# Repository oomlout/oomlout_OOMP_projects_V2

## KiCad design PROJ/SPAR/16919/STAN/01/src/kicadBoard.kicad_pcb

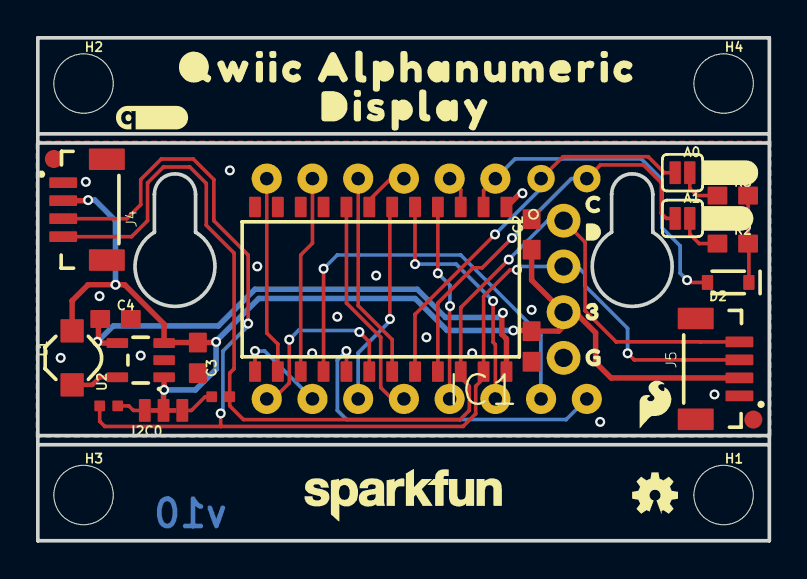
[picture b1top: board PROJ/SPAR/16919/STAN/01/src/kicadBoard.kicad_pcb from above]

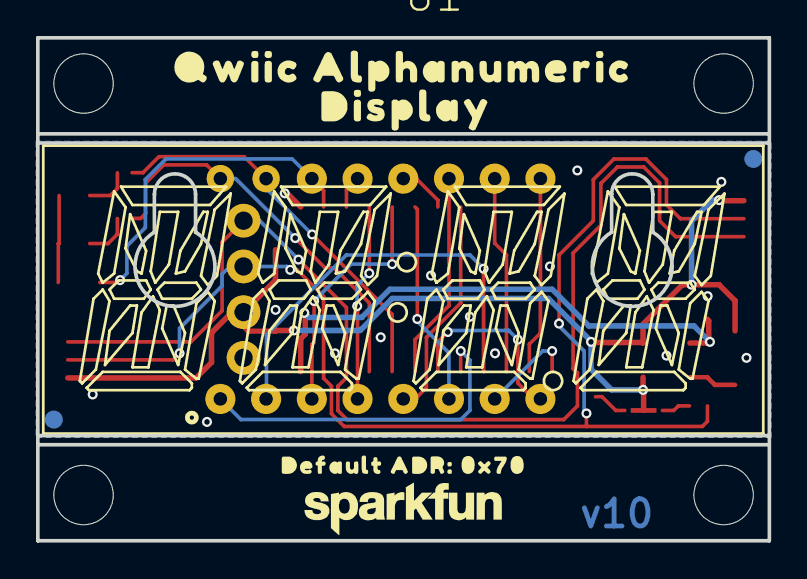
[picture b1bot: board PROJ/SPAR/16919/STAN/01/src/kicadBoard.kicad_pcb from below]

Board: 2 copper layers, 40.6 x 27.9 mm, 46 parts (7 on the bottom side), 27 nets.

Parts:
A0, A1: JUMPER-SMT_2_NO_SILK; SMT-JUMPER_2_NO_SILK
C1: 0.1uF; 0603
C2, C4: 10uF; 0603
C3: 4.7uF; 0603
D2: 250mA/100V; SOD-323
FD1, FD2, FD3, FD4: FIDUCIAL1X2; FIDUCIAL-1X2
FRAME1: FRAME-LETTER; CREATIVE_COMMONS
H1, H2, H3, H4: STAND-OFF
I2C0: JUMPER-SMT_3_2-NC_TRACE_NO-SILK; SMT-JUMPER_3_2-NC_TRACE_NO-SILK
IC1: VK16K33
J3: 1X04_NO_SILK
J4, J5: Vertical Qwiic Connector; JST04_1MM_VERT
L1: 4.7µH; INDUCTOR_4.7UH
LOGO1: OSHW-LOGOMINI; OSHW-LOGO-MINI
LOGO2, LOGO3: SFE_LOGO_NAME.1_INCH; SFE_LOGO_NAME_.1
LOGO4: SFE_LOGO_FLAME.1_INCH; SFE_LOGO_FLAME_.1
R2, R3: 39k; 0603
R4, R5: 4.7k; 0402-TIGHT
U1: Alphanumeric Display; SILSMART_DISPLAY
U2: XC9140; SOT23-5
U$1: DEFAULT_ADR#_0X700
U$3, U$7: MOUNTING_HOLE_M2-0.4X6
U$6: QWIIC_4MM
U$8, U$9: QWIIC_ALPHANUMERIC0
U$10, U$11: DISPLAY0
U$12: #A0#0
U$13: #A1#0
U$14: C0
U$15: D0
U$16: 30
U$17: G0

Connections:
3.3V: C1.1, C2.1, C3.1, I2C0.2, J3.2, J4.2, J5.2, L1.P$2, U2.1, U2.3
5V: C4.1, IC1.24, U2.4
COM_A: D2.A, IC1.2, U1.14
COM_B: IC1.3, U1.13
COM_C: IC1.4, U1.4
COM_D: IC1.5, U1.3
COM_E: IC1.6, U1.6
COM_F: IC1.7, U1.12
COM_G: IC1.8, U1.5
DIG_1A: A1.1, IC1.21, U1.16
DIG_1B: IC1.17, U1.1
DIG_2A: A0.1, IC1.20, U1.15
DIG_2B: IC1.16, U1.2
DIG_3A: IC1.19, U1.11
DIG_3B: IC1.15, U1.10
DIG_4A: IC1.18, U1.8
DIG_4B: IC1.14, U1.9
DIG_DP: IC1.13, U1.7
GND: C1.2, C2.2, C3.2, C4.2, IC1.1, J3.1, J4.1, J5.1, U2.2
unnamed: I2C0.3, R4.2
unnamed: A1.2, R2.1
unnamed: A0.2, R3.1
unnamed: I2C0.1, R5.2
unnamed: D2.C, R2.2, R3.2
unnamed: L1.P$1, U2.5
SCL: IC1.22, J3.4, J4.4, J5.4, R5.1
SDA: IC1.23, J3.3, J4.3, J5.3, R4.1

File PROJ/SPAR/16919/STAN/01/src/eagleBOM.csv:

"Part";"Value";"Device";"Package";"Description";"DESIGNER";"PROD_ID";"REV";"VALUE";
"A0";"JUMPER-SMT_2_NO_SILK";"JUMPER-SMT_2_NO_SILK";"SMT-JUMPER_2_NO_SILK";"Normally open jumper";"";"";"";"";
"A1";"JUMPER-SMT_2_NO_SILK";"JUMPER-SMT_2_NO_SILK";"SMT-JUMPER_2_NO_SILK";"Normally open jumper";"";"";"";"";
"C1";"0.1uF";"0.1UF-0603-25V-5%";"0603";"0.1µF ceramic capacitors";"";"CAP-08604";"";"0.1uF";
"C2";"10uF";"10UF-0603-6.3V-20%";"0603";"10.0µF ceramic capacitors";"";"CAP-11015";"";"10uF";
"C3";"4.7uF";"4.7UF-0603-6.3V-(10%)";"0603";"4.7µF ceramic capacitors";"";"CAP-08280";"";"4.7uF";
"C4";"10uF";"10UF-0603-6.3V-20%";"0603";"10.0µF ceramic capacitors";"";"CAP-11015";"";"10uF";
"D2";"250mA/100V";"DIODE-BAS16J";"SOD-323";"Diode";"";"DIO-09646";"";"250mA/100V";
"FD1";"FIDUCIAL1X2";"FIDUCIAL1X2";"FIDUCIAL-1X2";"Fiducial Alignment Points";"";"";"";"";
"FD2";"FIDUCIAL1X2";"FIDUCIAL1X2";"FIDUCIAL-1X2";"Fiducial Alignment Points";"";"";"";"";
"FD3";"FIDUCIAL1X2";"FIDUCIAL1X2";"FIDUCIAL-1X2";"Fiducial Alignment Points";"";"";"";"";
"FD4";"FIDUCIAL1X2";"FIDUCIAL1X2";"FIDUCIAL-1X2";"Fiducial Alignment Points";"";"";"";"";
"FRAME1";"FRAME-LETTER";"FRAME-LETTER";"CREATIVE_COMMONS";"Schematic Frame - Letter";"";"";"";"";
"H1";"STAND-OFF";"STAND-OFF";"STAND-OFF";"Stand Off";"";"";"";"";
"H2";"STAND-OFF";"STAND-OFF";"STAND-OFF";"Stand Off";"";"";"";"";
"H3";"STAND-OFF";"STAND-OFF";"STAND-OFF";"Stand Off";"";"";"";"";
"H4";"STAND-OFF";"STAND-OFF";"STAND-OFF";"Stand Off";"";"";"";"";
"I2C";"JUMPER-SMT_3_2-NC_TRACE_NO-SILK";"JUMPER-SMT_3_2-NC_TRACE_NO-SILK";"SMT-JUMPER_3_2-NC_TRACE_NO-SILK";"Normally closed trace jumper (2 of 2 connections)";"";"";"";"";
"IC1";"";"VK16K33VK16K33";"VK16K33";"HT16K33 24 SOP-A : RAM Mapping 16x8";"";"IC-16176";"";"";
"J3";"";"I2C_STANDARD_NO_SILK";"1X04_NO_SILK";"SparkFun I2C Standard Pinout Header";"";"";"";"";
"J4";"Vertical Qwiic Connector";"QWIIC_CONNECTOR";"JST04_1MM_VERT";"SparkFun I2C Standard Qwiic Connector";"";"CONN-14483";"";"Vertical Qwiic Connector";
"J5";"Vertical Qwiic Connector";"QWIIC_CONNECTOR";"JST04_1MM_VERT";"SparkFun I2C Standard Qwiic Connector";"";"CONN-14483";"";"Vertical Qwiic Connector";
"L1";"4.7µH";"INDUCTOR-CDRH-4.7UH";"INDUCTOR_4.7UH";"Inductors";"";"NDUC-10146";"";"4.7µH/±30%/1.2A";
"LOGO1";"OSHW-LOGOMINI";"OSHW-LOGOMINI";"OSHW-LOGO-MINI";"Open-Source Hardware (OSHW) Logo";"";"";"";"";
"LOGO2";"SFE_LOGO_NAME.1_INCH";"SFE_LOGO_NAME.1_INCH";"SFE_LOGO_NAME_.1";"SparkFun Font Logo";"";"";"";"";
"LOGO3";"SFE_LOGO_NAME.1_INCH";"SFE_LOGO_NAME.1_INCH";"SFE_LOGO_NAME_.1";"SparkFun Font Logo";"";"";"";"";
"LOGO4";"SFE_LOGO_FLAME.1_INCH";"SFE_LOGO_FLAME.1_INCH";"SFE_LOGO_FLAME_.1";"SparkFun Flame Logo";"";"";"";"";
"R2";"39k";"39KOHM-0603-1/10W-1%";"0603";"39kΩ resistor";"";"RES-12377";"";"39k";
"R3";"39k";"39KOHM-0603-1/10W-1%";"0603";"39kΩ resistor";"";"RES-12377";"";"39k";
"R4";"4.7k";"4.7KOHM-0402T-1/16W-1%";"0402-TIGHT";"4.7kΩ resistor";"";"RES-15343";"";"4.7k";
"R5";"4.7k";"4.7KOHM-0402T-1/16W-1%";"0402-TIGHT";"4.7kΩ resistor";"";"RES-15343";"";"4.7k";
"U$3";"MOUNTING_HOLE_M2-0.4X6";"MOUNTING_HOLE_M2-0.4X6";"MOUNTING_HOLE_M2-0.4X6";"";"";"";"";"";
"U$7";"MOUNTING_HOLE_M2-0.4X6";"MOUNTING_HOLE_M2-0.4X6";"MOUNTING_HOLE_M2-0.4X6";"";"";"";"";"";
"U1";"Alphanumeric Display";"SILSMART_DISPLAY-PINK";"SILSMART_DISPLAY";"14-Segment Alphanumeric LED Display from Silsmart Optoelectronics";"";"COMP-14892";"";"Alphanumeric Display";
"U2";"XC9140";"XC9140";"SOT23-5";"Simple 100mA max DC boost requiring only 3 external components. Useful for converting 3.3V or 4.2V up to 5V. 5.5V max output.";"";"VREG-14648";"";"";

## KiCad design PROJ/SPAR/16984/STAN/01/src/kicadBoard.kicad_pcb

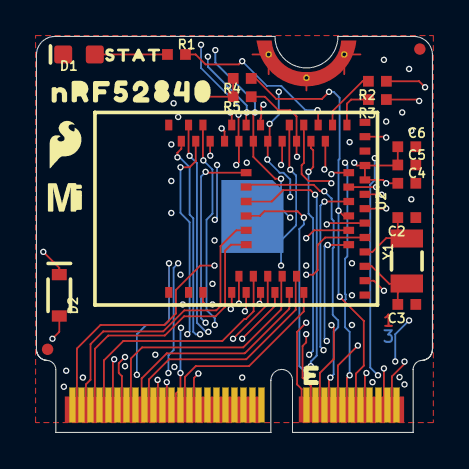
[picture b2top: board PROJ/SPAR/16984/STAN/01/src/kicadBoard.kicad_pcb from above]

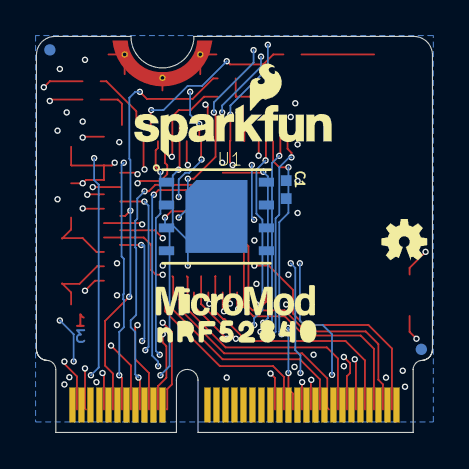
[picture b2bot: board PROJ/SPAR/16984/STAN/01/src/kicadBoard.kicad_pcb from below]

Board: 4 copper layers, 22.0 x 22.0 mm, 31 parts (8 on the bottom side), 59 nets.

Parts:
C1, C6: 0.1uF; 0402-TIGHT
C2, C3: 15pF; 0402-TIGHT
C4, C5: 10uF; 0402-TIGHT
D1: BLUE; LED-0603
D2: 1A/23V/620mV; SOD-323
FD1, FD2, FD3, FD4: FIDUCIALUFIDUCIAL; FIDUCIAL-MICRO
FRAME1: FRAME-LEDGER; CREATIVE_COMMONS
J1: MICROMOD-2222; M.2-CARD-E-22
LOGO1: SFE_LOGO_NAME_FLAME.1_INCH; SFE_LOGO_NAME_FLAME_.1
LOGO2: SFE_LOGO_FLAME.1_INCH; SFE_LOGO_FLAME_.1
LOGO3: OSHW-LOGOMINI; OSHW-LOGO-MINI
LOGO4: SPECIAL_INSTRUCTIONS-ORDERING; ORDERING_INSTRUCTIONS
R1: 1k; 0402-TIGHT
R2, R3: 27OHM; 0402-TIGHT
R4, R5: 10k; 0402-TIGHT
U1: W25QXX128MBIT-6X5; WSON-8-6X5
U2: MDBT50Q
U$1: MICROMOD_MI_LOGO_.35
U$2: STAT0
U$3, U$6: NRF528400
U$5: MICROMOD_LOGO_.35
Y1: 32.768kHz; CRYSTAL-SMD-3.2X1.5MM

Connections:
3.3V: C1.1, C4.1, C5.1, C6.1, D2.C, J1.72, R4.2, R5.2, U1.8, U2.28, U2.30
3.3V_EN: J1.4, U2.8
ADC0: J1.34, U2.20
ADC1: J1.38, U2.21
BATT_VIN/3: J1.49, U2.14
CTS1: J1.15, U2.26
D0: J1.10, U2.16
D1: J1.18, U2.25
FLASH_~CS: U1.1, U2.29
GND: C1.2, C2.1, C3.1, C4.2, C5.2, C6.2, D1.C, J1.1, J1.7, J1.33, J1.36, J1.39, J1.45, J1.75, J1.GND1, J1.GND2, J1.GND3, U1.4, U2.1, U2.2, U2.15, U2.33, U2.55
GPIO0: J1.40, U2.10
GPIO1: J1.42, U2.9
GPIO2: J1.44, U2.6
GPIO3: J1.46, U2.5
GPIO4: J1.48, U2.4
GPIO5: J1.73, U2.41
GPIO6: J1.71, U2.57
GPIO7: J1.69, U2.56
GPIO8: J1.67, U2.7
GPIO9/NFC1: J1.65, U2.52
GPIO10/NFC2: J1.63, U2.54
I2C_~INT: J1.16, U2.39
LED_BUILTIN: R1.2, U2.37
unnamed: R2.2, U2.35
unnamed: D1.A, R1.1
unnamed: R3.2, U2.34
unnamed: C3.2, U2.17, Y1.P$1
unnamed: D2.A, J1.2, J1.74
unnamed: C2.2, U2.18, Y1.P$2
PDM_CLK: J1.50, U2.49
PDM_DATA: J1.52, U2.19
PWM0: J1.32, U2.22
PWM1: J1.47, U2.38
RTS1: J1.13, U2.50
RX1: J1.19, U2.3
RX2: J1.20, U2.59
SCL: J1.14, U2.27
SCL1: J1.53, U2.48
SDA: J1.12, U2.24
SDA1: J1.51, U2.61
SDIO_DATA1: J1.66, U2.46
SDIO_DATA2: J1.68, U1.3, U2.45
SPI_CIPO: J1.61, U2.11
SPI_CIPO1/SDIO_DATA0: J1.64, U1.2, U2.43
SPI_COPI: J1.59, U2.12
SPI_COPI1/SDIO_CMD: J1.62, U1.5, U2.36
SPI_SCK: J1.57, U2.13
SPI_SCK1/SDIO_CLK: J1.60, U1.6, U2.42
SPI_~CS1/SDIO_DATA3: J1.70, U1.7, U2.47
SPI_~CS: J1.55, U2.44
SWDCK: J1.21, U2.53
SWDIO: J1.23, U2.51
TX1: J1.17, U2.60
TX2: J1.22, U2.58
USB_D+: J1.3, R2.1
USB_D-: J1.5, R3.1
V_USB: J1.9, U2.32
~BOOT: J1.11, R4.1, U2.23
~RESET: J1.6, R5.1, U2.40

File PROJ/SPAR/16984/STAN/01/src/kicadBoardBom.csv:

"Id";"Designator";"Package";"Quantity";"Designation";"Supplier and ref";
1;"R1";"0402-TIGHT";1;"1k";;;
2;"R5,R4";"0402-TIGHT";2;"10k";;;
3;"J1";"M.2-CARD-E-22";1;"MICROMOD-2222";;;
4;"R3,R2";"0402-TIGHT";2;"27OHM";;;
5;"U$6,U$3";"NRF528400";2;"";;;
6;"Y1";"CRYSTAL-SMD-3.2X1.5MM";1;"32.768kHz";;;
7;"D2";"SOD-323";1;"1A/23V/620mV";;;
8;"C2,C3";"0402-TIGHT";2;"15pF";;;
9;"C4,C5";"0402-TIGHT";2;"10uF";;;
10;"U$1";"MICROMOD_MI_LOGO_.35";1;"";;;
11;"FD1,FD2,FD3,FD4";"FIDUCIAL-MICRO";4;"FIDUCIALUFIDUCIAL";;;
12;"FRAME1";"CREATIVE_COMMONS";1;"FRAME-LEDGER";;;
13;"C6,C1";"0402-TIGHT";2;"0.1uF";;;
14;"LOGO2";"SFE_LOGO_FLAME_.1";1;"SFE_LOGO_FLAME.1_INCH";;;
15;"D1";"LED-0603";1;"BLUE";;;
16;"U2";"MDBT50Q";1;"MDBT50Q";;;
17;"LOGO4";"ORDERING_INSTRUCTIONS";1;"SPECIAL_INSTRUCTIONS-ORDERING";;;
18;"U$2";"STAT0";1;"";;;
19;"U1";"WSON-8-6X5";1;"W25QXX128MBIT-6X5";;;
20;"LOGO3";"OSHW-LOGO-MINI";1;"OSHW-LOGOMINI";;;
21;"LOGO1";"SFE_LOGO_NAME_FLAME_.1";1;"SFE_LOGO_NAME_FLAME.1_INCH";;;
22;"U$5";"MICROMOD_LOGO_.35";1;"";;;

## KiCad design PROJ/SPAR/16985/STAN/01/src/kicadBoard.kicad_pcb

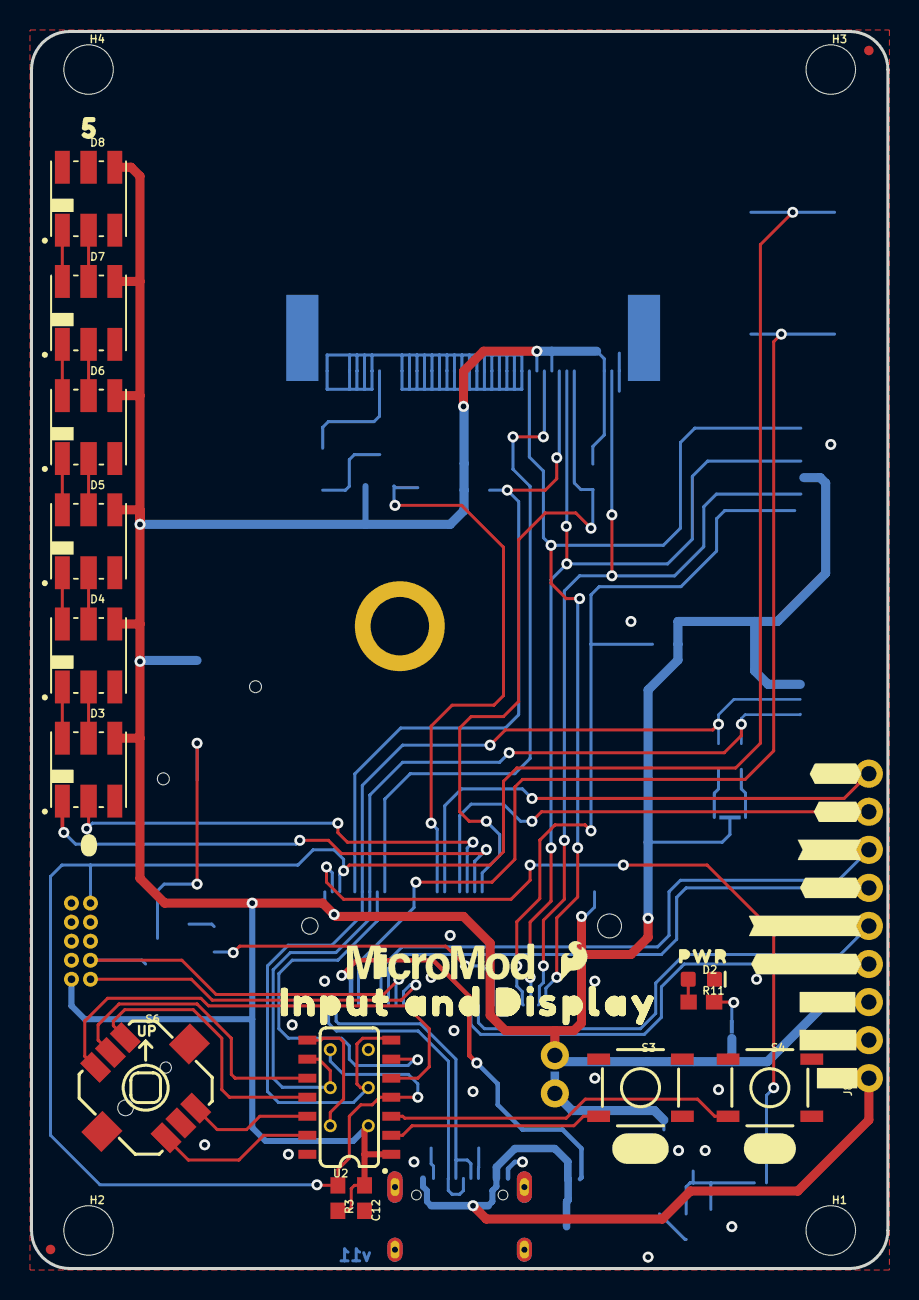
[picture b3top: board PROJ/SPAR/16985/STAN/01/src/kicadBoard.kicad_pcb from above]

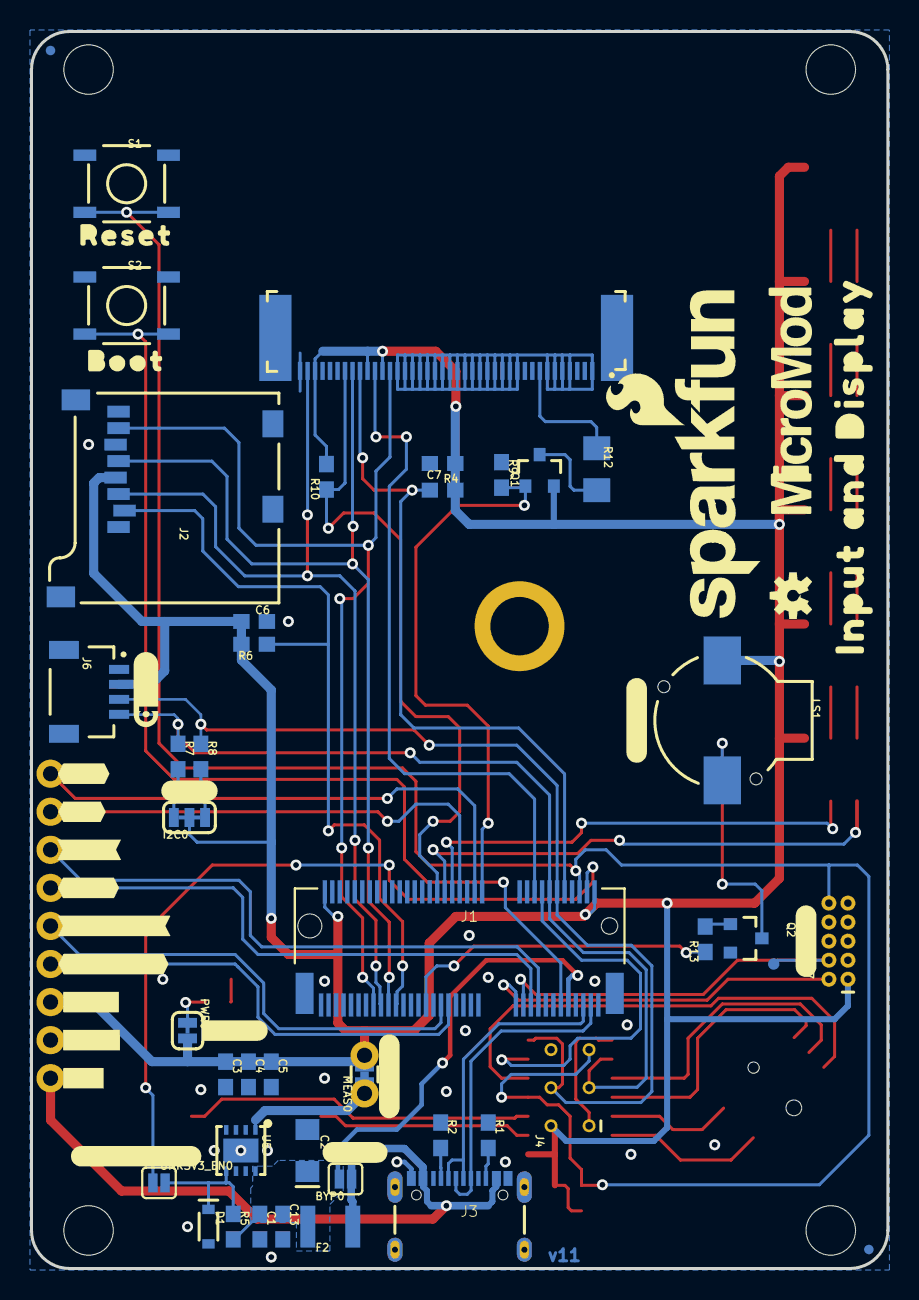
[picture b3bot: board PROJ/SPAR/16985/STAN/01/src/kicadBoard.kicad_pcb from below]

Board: 2 copper layers, 57.1 x 82.6 mm, 107 parts (66 on the bottom side), 61 nets.

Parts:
BYP0: JUMPER-SMT_2_NO_SILK; SMT-JUMPER_2_NO_SILK
C1, C4, C6, C7, C12: 0.1uF; 0603
C2: 10uF; EIA3216
C3: 1.0uF; 0603
C5, C13: 0.22uF; 0603
D1: 3.3V; SOD-323
D2: RED; LED-0603
D3, D4, D5, D6, D7, D8: APA102-5050
F2: 6V/2A; 1210
FD1, FD2, FD3, FD4: FIDUCIALUFIDUCIAL; FIDUCIAL-MICRO
FRAME1: FRAME-LETTER; CREATIVE_COMMONS
FRAME2: FRAME-LETTERNO_PACKAGE; DUMMY
H1, H2, H3, H4: STAND-OFF
H5: STAND-OFF; STAND-OFF-REFLOW-M2.5
I2C0: SMT-JUMPER_3_2-NC_TRACE_SILK
J1: MICROMOD-2222-C; M.2-CONNECTOR-E
J2: MICRO-SD; MICRO-SD-SOCKET
J3: USB-C_Prog; USB-C-16P-2LAYER-PADS
J4: AVR_SPI_PROG_3X2TESTPOINTS; 2X3_TEST_POINTS
J5: 2.4" TFT; FPC05040-17204
J6: QWIIC_RA; JST04_1MM_RA
J7: CORTEX_JTAG_DEBUG; 2X5-PTH-1.27MM-NO_SILK
J8: 1X09_NO_SILK
LOGO1: SFE_LOGO_NAME_FLAME.2_INCH; SFE_LOGO_NAME_FLAME_.2
LOGO2: QWIIC_LOGO_5MM; QWIIC_5MM
LOGO3: OSHW-LOGOS; OSHW-LOGO-S
LS1: Buzzer; BUZZER-CCV
MEAS0: COMBO-JUMPER_2_NC_TRACE
PWR0: SMT-JUMPER_2_NC_TRACE_SILK
Q1: 1.1A/600mΩ; SOT23-3
Q2: 600mA/40V; SOT23-3
R1, R2: 5.1k; 0603
R3, R4, R5, R6, R9, R10: 100k; 0603
R7, R8: 2.2k; 0603
R11, R13: 1k; 0603
R12: 10; 1206
S1: Reset; TACTILE_SWITCH_SMD_5.2MM
S2: BOOT; TACTILE_SWITCH_SMD_5.2MM
S3, S4: MOMENTARY-SWITCH-SPST-SMD-5.2MM-TALL; TACTILE_SWITCH_SMD_5.2MM
S6: Joystick; JOYSTICK_MINI
TP1: PAD.03X.03
U2: ATTINY84; SO14
U5: AP7361C-33FGE; UDFN-8
U$1: MICROMOD_LOGO_.5
U$2, U$16, U$17: INPUT_AND_DISPLAY0
U$3: SFE_LOGO_FLAME_.1
U$4: BOOT0
U$5: #A#0
U$6: #B#0
U$7: 00
U$8: 50
U$9: RESET0
U$10: MICROMOD_LOGO_.6
U$11: #MEAS#0
U$12: #I2C#0
U$13: PWR0
U$14: #BYP#0
U$15: #SWD#0
U$18, U$38: #5V#0
U$19: #PWR#0
U$20: #3V3_CTRL#0
U$21: #PWM1#0
U$22, U$23: #A0#0
U$24, U$25: #A1#0
U$26, U$27: #TX1#0
U$28, U$31: #3V3#0
U$29, U$30: #GND#0
U$32, U$33: #RX1#0
U$34, U$35: #CAN#RX#0
U$36, U$37: #CAN#TX#0
UNK3V3_EN0: SMT-JUMPER_2_NO_SILK

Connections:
3.3V: C3.1, C4.1, C5.1, C6.1, C7.1, C12.1, D3.P4, D4.P4, D5.P4, D6.P4, D7.P4, D8.P4, I2C0.2, J1.2, J1.74, J2.VCC, J4.2, J5.29, J5.31, J5.38, J6.2, J7.1, J8.3, LS1.+, MEAS0.2, MEAS0.4, PWR0.2, Q1.2, R3.2, R4.2, R6.2, R10.2, U2.1
3.3V_EN: J1.4, UNK3V3_EN0.1
A0: J1.34, J8.9
A1: J1.38, J8.8
BTN_A: S3.3, U2.2
BTN_B: S4.3, U2.3
BTN_CENTER: S6.CTR, U2.10
BTN_DOWN: S6.D, U2.13
BTN_LEFT: S6.C, U2.5
BTN_RIGHT: S6.B, U2.12
BTN_UP: S6.A, U2.11
BUZZER: J1.47, R13.1
CAN-RX: J1.41, J8.4
CAN-TX: J1.43, J8.5
DISP_D/~C: J1.18, J5.30
ENABLE: D1.C, R5.1, U5.5, UNK3V3_EN0.2
GND: C1.2, C2.-, C3.2, C4.2, C5.2, C6.2, C7.2, C12.2, C13.2, D1.A, D2.C, D3.P3, D4.P3, D5.P3, D6.P3, D7.P3, D8.P3, H5.1, J1.1, J1.7, J1.33, J1.36, J1.39, J1.45, J1.75, J2.CD1, J2.GND, J3.GND, J3.GND2, J4.6, J5.1, J5.4, J5.5, J5.6, J5.7, J5.11, J5.12, J5.13, J5.14, J5.15, J5.16, J5.17, J5.18, J5.19, J5.20, J5.21, J5.22, J5.23, J5.24, J5.25, J5.26, J5.27, J5.40, J6.1, J7.3, J7.5, J7.9, J8.2, Q2.2, R1.1, R2.1, R9.1, S1.1, S1.2, S2.1, S2.2, S3.1, S4.1, S6.GND, U2.14, U5.4, U5.EP
LED_CLK: D3.P2, J1.40
LED_DATA: D3.P1, J1.42
MISO_ATTINY: J4.1, U2.8
unnamed: I2C0.3, R7.2
unnamed: I2C0.1, R8.2
unnamed: J5.8, R12.1
unnamed: Q1.3, R12.2
unnamed: LS1.-, Q2.3
unnamed: Q2.1, R13.2
unnamed: D3.P5, D4.P2
unnamed: D3.P6, D4.P1
unnamed: J3.A5, R2.2
unnamed: J3.B5, R1.2
unnamed: PWR0.1, R11.2
unnamed: D2.A, R11.1
unnamed: MEAS0.1, MEAS0.3, U5.1
unnamed: D4.P5, D5.P2
unnamed: D4.P6, D5.P1
unnamed: D5.P5, D6.P2
unnamed: D5.P6, D6.P1
unnamed: D6.P5, D7.P2
unnamed: D6.P6, D7.P1
unnamed: D7.P5, D8.P2
unnamed: D7.P6, D8.P1
RX1: J1.19, J8.6
SCL: J1.14, J4.3, J6.4, R7.1, U2.9
SDA: J1.12, J4.4, J6.3, R8.1, U2.7
SPI_CIPO: J1.61, J2.DO, J5.28
SPI_COPI: J1.59, J2.DI, J5.39
SPI_SCK: J1.57, J2.SCLK, J5.33
SWDCK: J1.21, J7.4, TP1.P$1
SWDIO: J1.23, J7.2
TX1: J1.17, J8.7
USB_D+: J1.3, J3.A6, J3.B6
USB_D-: J1.5, J3.A7, J3.B7
VIN: BYP0.2, C1.1, C2.+, C13.1, F2.2, J1.9, R5.2, U5.8
V_USB: BYP0.1, F2.1, J3.VBUS1, J3.VBUS2, J8.1
~BOOT: J1.11, S2.3, S2.4
~DISP_BL: J1.32, Q1.1, R9.2
~DISP_CS: J1.10, J5.32, R4.1
~DISP_RST: J1.44, J5.34, R10.1
~INT: J1.16, U2.6
~RESET: J1.6, J4.5, J7.10, R3.1, S1.3, S1.4, U2.4
~SD_CS: J1.55, J2.CS, R6.1

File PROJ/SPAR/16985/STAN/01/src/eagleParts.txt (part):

Partlist

Exported from boardEagle.brd at 20/08/2022 16:38

EAGLE Version 9.6.2 Copyright (c) 1988-2020 Autodesk, Inc.

Assembly variant: 

Part     Value                                Package                      Library                     Position (inch)       Orientation

3V3_EN                                        SMT-JUMPER_2_NO_SILK         SparkFun-Jumpers            (1.915 0.225)         MR0
BYP      JUMPER-SMT_2_NO_SILK                 SMT-JUMPER_2_NO_SILK         SparkFun-Jumpers            (1.425 0.235)         MR180
C1       0.1uF                                0603                         SparkFun-Capacitors         (1.65 0.11)           MR270
C2       10uF                                 EIA3216                      SparkFun-Capacitors         (1.525 0.31)          MR270
C3       1.0uF                                0603                         SparkFun-Capacitors         (1.74 0.51)           MR270
C4       0.1uF                                0603                         SparkFun-Capacitors         (1.68 0.51)           MR270
C5       0.22uF                               0603                         SparkFun-Capacitors         (1.62 0.51)           MR270
C6       0.1uF                                0603                         SparkFun-Capacitors         (1.665 1.7)           MR0
C7       0.1uF                                0603                         SparkFun-Capacitors         (1.17 2.115)          MR180
C12      0.1uF                                0603                         SparkFun-Capacitors         (0.875 0.185)         R270
C13      0.22uF                               0603                         SparkFun-Capacitors         (1.59 0.11)           MR270
D1       3.3V                                 SOD-323                      SparkFun-DiscreteSemi       (1.785 0.11)          MR270
D2       RED                                  LED-0603                     SparkFun-LED                (1.76 0.76)           R0
D3       APA102-5050                          APA102-5050                  SparkFun-LED                (0.15 1.31062992)     R0
D4       APA102-5050                          APA102-5050                  SparkFun-LED                (0.15 1.61062992)     R0
D5       APA102-5050                          APA102-5050                  SparkFun-LED                (0.15 1.91062992)     R0
D6       APA102-5050                          APA102-5050                  SparkFun-LED                (0.15 2.21062992)     R0
D7       APA102-5050                          APA102-5050                  SparkFun-LED                (0.15 2.51062992)     R0
D8       APA102-5050                          APA102-5050                  SparkFun-LED                (0.15 2.81062992)     R0
F2       6V/2A                                1210                         SparkFun-Fuses              (1.465 0.11)          MR180
FD1      FIDUCIALUFIDUCIAL                    FIDUCIAL-MICRO               SparkFun-Aesthetics         (0.05 0.05)           MR0
FD2      FIDUCIALUFIDUCIAL                    FIDUCIAL-MICRO               SparkFun-Aesthetics         (0.05 0.05)           R0
FD3      FIDUCIALUFIDUCIAL                    FIDUCIAL-MICRO               SparkFun-Aesthetics         (2.2 3.2)             R0
FD4      FIDUCIALUFIDUCIAL                    FIDUCIAL-MICRO               SparkFun-Aesthetics         (2.2 3.2)             MR0
H5       STAND-OFF                            STAND-OFF-REFLOW-M2.5        SparkFun-Hardware           (0.96771654 1.68759843) MR90
I2C                                           SMT-JUMPER_3_2-NC_TRACE_SILK SparkFun-Jumpers            (1.835 1.185)         MR180
J1       MICROMOD-2222-C                      M.2-CONNECTOR-E              SparkFun-MicroMod           (1.125 0.9)           MR0
J2       MICRO-SD                             MICRO-SD-SOCKET              SparkFun-Connectors         (1.6 2.3)             MR90
J3       USB-C_Prog                           USB-C-16P-2LAYER-PADS        SparkFun-Connectors         (1.125 0.25)          MR0
J4       AVR_SPI_PROG_3X2TESTPOINTS           2X3_TEST_POINTS              SparkFun-Connectors         (0.835 0.475)         MR90
J5       2.4" TFT                             FPC05040-17204               SparkFun-Displays           (1.16043307 2.38188976) MR180
J6       QWIIC_RA                             JST04_1MM_RA                 SparkFun-Connectors         (2.02 1.515)          MR270
J7       CORTEX_JTAG_DEBUG                    2X5-PTH-1.27MM-NO_SILK       SparkFun-Connectors         (0.13 0.86)           MR90
J8                                            1X09_NO_SILK                 SparkFun-Connectors         (2.2 0.5)             R90
LS1      Buzzer                               BUZZER-CCV                   SparkFun-Electromechanical  (0.435 1.44)          MR90
MEAS                                          COMBO-JUMPER_2_NC_TRACE      SparkFun-Jumpers            (1.375 0.51)          MR90
PWR                                           SMT-JUMPER_2_NC_TRACE_SILK   SparkFun-Jumpers            (1.84 0.625)          MR270
Q1       1.1A/600m?                           SOT23-3                      SparkFun-DiscreteSemi       (0.915 2.095)         MR0
Q2       600mA/40V                            SOT23-3                      SparkFun-DiscreteSemi       (0.37437008 0.86740157) MR270
R1       5.1k                                 0603                         SparkFun-Resistors          (1.05 0.35)           MR270
R2       5.1k                                 0603                         SparkFun-Resistors          (1.175 0.35)          MR270
R3       100k                                 0603                         SparkFun-Resistors          (0.805 0.185)         R270
R4       100k                                 0603                         SparkFun-Resistors          (1.17 2.045)          MR0
R5       100k                                 0603                         SparkFun-Resistors          (1.72 0.11)           MR270
R6       100k                                 0603                         SparkFun-Resistors          (1.665 1.64)          MR180
R7       2.2k                                 0603                         SparkFun-Resistors          (1.865 1.345)         MR270
R8       2.2k                                 0603                         SparkFun-Resistors          (1.805 1.345)         MR270
R9       100k                                 0603                         SparkFun-Resistors          (1.015 2.085)         MR270
R10      100k                                 0603                         SparkFun-Resistors          (1.475 2.08)          MR90
R11      1k                                   0603                         SparkFun-Resistors          (1.76 0.7)            R0
R12      10                                   1206                         SparkFun-Resistors          (0.765 2.1)           MR270
R13      1k                                   0603                         SparkFun-Resistors          (0.48 0.865)          MR90
S1       Reset                                TACTILE_SWITCH_SMD_5.2MM     SparkFun-Switches           (2 2.85)              MR0
S2       BOOT                                 TACTILE_SWITCH_SMD_5.2MM     SparkFun-Switches           (2 2.53)              MR0
S3       MOMENTARY-SWITCH-SPST-SMD-5.2MM-TALL TACTILE_SWITCH_SMD_5.2MM     SparkFun-Switches           (1.6 0.475)           R0
S4       MOMENTARY-SWITCH-SPST-SMD-5.2MM-TALL TACTILE_SWITCH_SMD_5.2MM     SparkFun-Switches           (1.94 0.475)          R0
S6       Joystick                             JOYSTICK_MINI                SparkFun-Switches           (0.3 0.475)           R315
TP1                                           PAD.03X.03                   SparkFun-Connectors         (0.3 0.8)             MR0
U2       ATTINY84                             SO14                         SparkFun-IC-Microcontroller (0.835 0.45)          R90
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
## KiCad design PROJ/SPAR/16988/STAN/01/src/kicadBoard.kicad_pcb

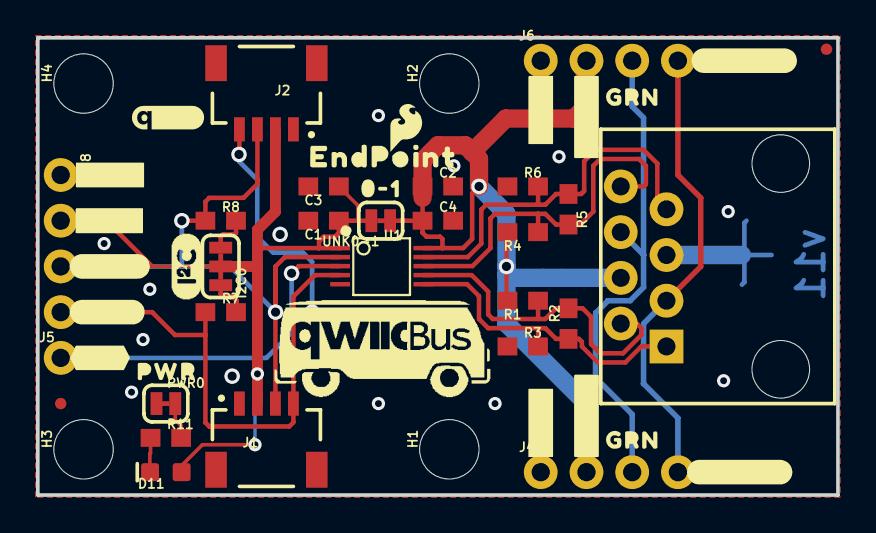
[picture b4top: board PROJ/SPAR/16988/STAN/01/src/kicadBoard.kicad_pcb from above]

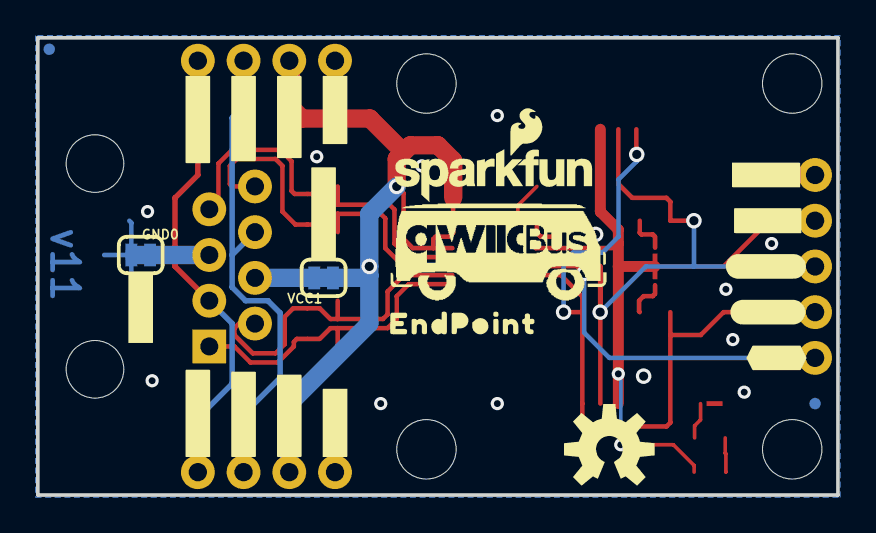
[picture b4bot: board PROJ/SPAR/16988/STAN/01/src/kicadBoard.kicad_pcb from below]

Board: 2 copper layers, 44.5 x 25.4 mm, 76 parts (23 on the bottom side), 18 nets.

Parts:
C1, C2: 0.1uF; 0603
C3, C4: 1.0uF; 0603
D11: RED; LED-0603
FD1, FD2, FD3, FD4: FIDUCIALUFIDUCIAL; FIDUCIAL-MICRO
FRAME1: FRAME-LETTER; CREATIVE_COMMONS
GND0: JUMPER-SMT_2_NC_TRACE_SILK; SMT-JUMPER_2_NC_TRACE_SILK
H1, H2, H3, H4: STAND-OFF
I2C0: JUMPER-SMT_3_2-NC_TRACE_SILK; SMT-JUMPER_3_2-NC_TRACE_SILK
J1, J2: QWIIC; JST04_1MM_RA
J3: RJ45; RJ45-8
J4, J6, J8: 1X04_NO_SILK
J5: 1X01_NO_SILK
LOGO1: OSHW-LOGOM; OSHW-LOGO-M
LOGO2: REVISION
LOGO3: QWIIC_LOGO_4MM; QWIIC_4MM
LOGO4: SFE_LOGO_NAME_FLAME.1_INCH; SFE_LOGO_NAME_FLAME_.1
LOGO5: SFE_LOGO_FLAME.1_INCH; SFE_LOGO_FLAME_.1
PWR0: JUMPER-SMT_2_NC_TRACE_SILK; SMT-JUMPER_2_NC_TRACE_SILK
R1, R3, R4, R6: 390; 0603
R2, R5: 100; 0603
R7, R8: 4.7k; 0603
R11: 1k; 0603
U1: PCA9615; TSSOP10
U$1: I2C
U$2, U$29: GRN0
U$3, U$4, U$5, U$6, U$13, U$33, U$34: #GND#0
U$7, U$8: #3V3#0
U$9, U$15: #SDA#0
U$10, U$16: #SCL#0
U$11, U$17: #EN#0
U$12: #VDDA#0
U$14, U$18: #GND2#0
U$19, U$22: #GRNW#0
U$20, U$21, U$31, U$32: #VCC1#0
U$23, U$28: QWIICBUS#WORKING#LOGO#JPG
U$24, U$30: #VCC2#0
U$25: 0#10
U$26, U$35: ENDPOINT0
U$27: PWR0
UNK0-1: JUMPER-SMT_2_NC_TRACE_SILK; SMT-JUMPER_2_NC_TRACE_SILK
VCC1: JUMPER-SMT_2_NC_TRACE_SILK; SMT-JUMPER_2_NC_TRACE_SILK

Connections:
DSCL_N: J3.1, R2.1, R3.2, U1.6
DSCL_P: J3.2, R1.1, R2.2, U1.7
DSDA_N: J3.7, R5.1, R6.2, U1.9
DSDA_P: J3.8, R4.1, R5.2, U1.8
EN: J5.1, U1.3
GND: C1.2, C2.2, C3.2, C4.2, GND0.1, J1.1, J2.1, J4.1, J6.1, J8.1, PWR0.1, R3.1, R6.1, U1.5
GRN_N: J3.6, J4.3, J6.3
GRN_P: J3.3, J4.4, J6.4
unnamed: J3.4, VCC1.2
unnamed: GND0.2, J3.5
unnamed: I2C0.1, R8.2
unnamed: I2C0.3, R7.2
unnamed: D11.C, R11.1
unnamed: PWR0.2, R11.2
SCL: J1.4, J2.4, J8.4, R7.1, U1.4
SDA: J1.3, J2.3, J8.3, R8.1, U1.2
VCC: C1.1, C3.1, D11.A, I2C0.2, J1.2, J2.2, J8.2, U1.1, UNK0-1.2
VCC_1: C2.1, C4.1, J4.2, J6.2, R1.2, R4.2, U1.10, UNK0-1.1, VCC1.1

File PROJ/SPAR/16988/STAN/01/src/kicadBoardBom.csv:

"Id";"Designator";"Package";"Quantity";"Designation";"Supplier and ref";
1;"R2,R5";"0603";2;"100";;;
2;"R3,R4,R1,R6";"0603";4;"390";;;
3;"UNK0-1,PWR0,GND0,VCC1";"SMT-JUMPER_2_NC_TRACE_SILK";4;"JUMPER-SMT_2_NC_TRACE_SILK";;;
4;"J5";"1X01_NO_SILK";1;"";;;
5;"U$28,U$23";"QWIICBUS#WORKING#LOGO#JPG";2;"";;;
6;"H2,H4,H3,H1";"STAND-OFF";4;"STAND-OFF";;;
7;"U$1";"I2C";1;"";;;
8;"U$2,U$29";"GRN0";2;"";;;
9;"U$22,U$19";"#GRNW#0";2;"";;;
10;"U$34,U$3,U$5,U$4,U$33,U$13,U$6";"#GND#0";7;"";;;
11;"FRAME1";"CREATIVE_COMMONS";1;"FRAME-LETTER";;;
12;"J2,J1";"JST04_1MM_RA";2;"QWIIC";;;
13;"D11";"LED-0603";1;"RED";;;
14;"C3,C4";"0603";2;"1.0uF";;;
15;"U$20,U$32,U$21,U$31";"#VCC1#0";4;"";;;
16;"C1,C2";"0603";2;"0.1uF";;;
17;"FD1,FD2,FD3,FD4";"FIDUCIAL-MICRO";4;"FIDUCIALUFIDUCIAL";;;
18;"J4,J8,J6";"1X04_NO_SILK";3;"";;;
19;"LOGO5";"SFE_LOGO_FLAME_.1";1;"SFE_LOGO_FLAME.1_INCH";;;
20;"I2C0";"SMT-JUMPER_3_2-NC_TRACE_SILK";1;"JUMPER-SMT_3_2-NC_TRACE_SILK";;;
21;"R7,R8";"0603";2;"4.7k";;;
22;"U$10,U$16";"#SCL#0";2;"";;;
23;"LOGO3";"QWIIC_4MM";1;"QWIIC_LOGO_4MM";;;
24;"U$27";"PWR0";1;"";;;
25;"U$11,U$17";"#EN#0";2;"";;;
26;"U$35,U$26";"ENDPOINT0";2;"";;;
27;"U$7,U$8";"#3V3#0";2;"";;;
28;"J3";"RJ45-8";1;"RJ45";;;
29;"R11";"0603";1;"1k";;;
30;"U1";"TSSOP10";1;"PCA9615";;;
31;"LOGO2";"REVISION";1;"REVISION";;;
32;"U$25";"0#10";1;"";;;
33;"U$9,U$15";"#SDA#0";2;"";;;
34;"U$14,U$18";"#GND2#0";2;"";;;
35;"LOGO1";"OSHW-LOGO-M";1;"OSHW-LOGOM";;;
36;"U$30,U$24";"#VCC2#0";2;"";;;
37;"U$12";"#VDDA#0";1;"";;;
38;"LOGO4";"SFE_LOGO_NAME_FLAME_.1";1;"SFE_LOGO_NAME_FLAME.1_INCH";;;

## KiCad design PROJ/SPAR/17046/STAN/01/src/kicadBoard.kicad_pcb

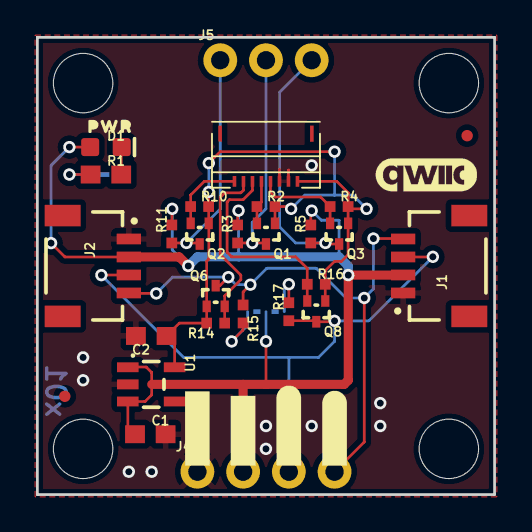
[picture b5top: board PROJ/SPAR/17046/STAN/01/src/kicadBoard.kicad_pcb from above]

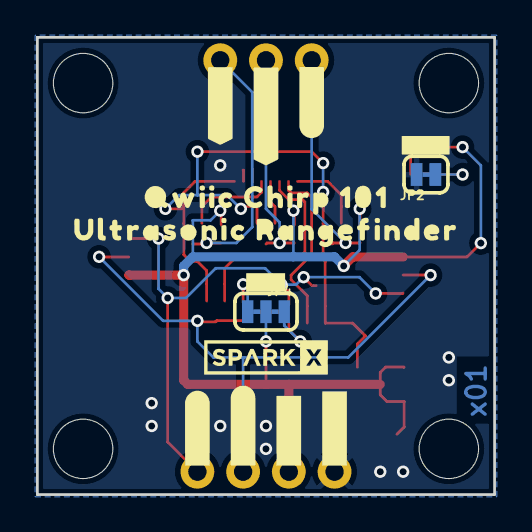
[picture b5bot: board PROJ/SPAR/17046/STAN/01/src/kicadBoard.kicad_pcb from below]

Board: 2 copper layers, 25.4 x 25.4 mm, 49 parts (14 on the bottom side), 17 nets.

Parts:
C1, C2: 1.0uF; 0603
D1: RED; LED-0603
FD1, FD2: FIDUCIALUFIDUCIAL; FIDUCIAL-MICRO
FRAME1: FRAME-LETTERNO_PACKAGE; DUMMY
J1, J2: QWIIC_RIGHT_ANGLE; JST04_1MM_RA
J4: 1X04_NO_SILK
J5: 1X03_NO_SILK
JP2: SMT-JUMPER_2_NC_TRACE_SILK
JP4: I2C PU; SMT-JUMPER_3_2-NC_TRACE_SILK
Q1, Q2, Q3, Q6, Q8: 20V/0.2A/8MHz/1.2Ω/1Vth; SOT-416FL
R1: 1k; 0603
R2, R3, R4, R5, R10, R11, R14, R15, R16, R17: 2.2k; 0402-TIGHT
U1: AP2127K-1.8V; SOT23-5
U$1: MOD-CH101_CONNECTOR; FPC_MOLEX5034800800
U$2: QWIIC_BOARD_OUTLINEH; QWIIC_BOARD_MOUNT_HOLES
U$3, U$13: #_3V3#1
U$4, U$14: #_GND#0
U$5, U$12: #_SDA#2
U$6, U$11: #_SCL#3
U$7: QWIIC_CHIRP_1017
U$8: ULTRASONIC_RANGEFINDER8
U$9: #I�C#1019
U$10: #LED#1018
U$15: ##INT_##0
U$16: ##RST_##1
U$17: #PROG_#5
U$18: SPARKX-SMALL
U$19: QWIIC_COPYRIGHT_SMALL
U$20: PWR0

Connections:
1.8V: C2.1, Q1.1, Q2.1, Q3.1, Q6.1, Q8.1, R2.2, R4.2, R10.2, R14.2, R16.2, U1.5, U$1.1
GND: C1.2, C2.2, J1.1, J2.1, J4.1, JP2.2, U1.2, U$1.2, U$1.3
INT_HI: J5.1, Q2.3, R11.1
INT_LO: Q2.2, R10.1, U$1.8
unnamed: D1.C, R1.2
unnamed: JP4.3, R15.2
unnamed: JP4.1, R17.2
unnamed: JP2.1, R1.1
PROG_HI: J5.2, Q1.3, R3.1
PROG_LO: Q1.2, R2.1, U$1.5
RST_HI: J5.3, Q3.3, R5.1
RST_LO: Q3.2, R4.1, U$1.4
SCL_HI: J1.4, J2.4, J4.4, Q6.3, R15.1
SCL_LO: Q6.2, R14.1, U$1.7
SDA_HI: J1.3, J2.3, J4.3, Q8.3, R17.1
SDA_LO: Q8.2, R16.1, U$1.6
VIN: C1.1, D1.A, J1.2, J2.2, J4.2, JP4.2, R3.2, R5.2, R11.2, U1.1, U1.3

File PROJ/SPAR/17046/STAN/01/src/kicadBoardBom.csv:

"Id";"Designator";"Package";"Quantity";"Designation";"Supplier and ref";
1;"C1,C2";"0603";2;"1.0uF";;;
2;"U$1";"FPC_MOLEX5034800800";1;"MOD-CH101_CONNECTOR";;;
3;"Q6,Q1,Q3,Q2,Q8";"SOT-416FL";5;"20V/0.2A/8MHz/1.2Ω/1Vth";;;
4;"J2,J1";"JST04_1MM_RA";2;"QWIIC_RIGHT_ANGLE";;;
5;"R1";"0603";1;"1k";;;
6;"R4,R2,R14,R11,R17,R5,R15,R10,R16,R3";"0402-TIGHT";10;"2.2k";;;
7;"U$4,U$14";"#_GND#0";2;"";;;
8;"U$3,U$13";"#_3V3#1";2;"";;;
9;"FRAME1";"DUMMY";1;"FRAME-LETTERNO_PACKAGE";;;
10;"U$5,U$12";"#_SDA#2";2;"";;;
11;"FD2,FD1";"FIDUCIAL-MICRO";2;"FIDUCIALUFIDUCIAL";;;
12;"U$19";"QWIIC_COPYRIGHT_SMALL";1;"";;;
13;"D1";"LED-0603";1;"RED";;;
14;"U$20";"PWR0";1;"";;;
15;"U$2";"QWIIC_BOARD_MOUNT_HOLES";1;"QWIIC_BOARD_OUTLINEH";;;
16;"U$6,U$11";"#_SCL#3";2;"";;;
17;"J4";"1X04_NO_SILK";1;"";;;
18;"U1";"SOT23-5";1;"AP2127K-1.8V";;;
19;"J5";"1X03_NO_SILK";1;"";;;
20;"U$18";"SPARKX-SMALL";1;"";;;
21;"U$7";"QWIIC_CHIRP_1017";1;"";;;
22;"U$8";"ULTRASONIC_RANGEFINDER8";1;"";;;
23;"U$10";"#LED#1018";1;"";;;
24;"JP2";"SMT-JUMPER_2_NC_TRACE_SILK";1;"";;;
25;"U$17";"#PROG_#5";1;"";;;
26;"U$9";"#I�C#1019";1;"";;;
27;"U$15";"##INT_##0";1;"";;;
28;"U$16";"##RST_##1";1;"";;;
29;"JP4";"SMT-JUMPER_3_2-NC_TRACE_SILK";1;"I2C PU";;;

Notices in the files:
parts and their libraries:
RELEASED UNDER THE CREATIVE COMMONS ATTRIBUTION SHARE-ALIKE 4.0 LICENSE
HTTPS://CREATIVECOMMONS.ORG/LICENSES/BY-SA/4.0
